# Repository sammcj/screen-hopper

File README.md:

# Screen Hopper: a smart KVM switch

This is a USB input switcher that lets you use you mouse and keyboard with two computers by just dragging the mouse cursor from one screen to the other. It's like Logitech Flow, Mouse without Borders, Synergy or Apple Universal Control, but it works entirely in hardware. No special software is required on the computers. It works with Windows, Linux and Mac.

Here's a [demo video](https://www.youtube.com/watch?v=z24jG9Nh5gk).

This project is derived from [HID Remapper](https://github.com/jfedor2/hid-remapper) so it inherits all the nice features like input remapping, sensitivity adjustment, polling rate overclocking and more. Check out that project's documentation to see its full potential.

Screen shapes and their relative position are configurable [through a web browser](https://www.jfedor.org/screen-hopper-config/) using WebHID (Chrome or Chrome-based browser required).

In addition to dragging the cursor from one screen to the other, you can also map a key or button to switch between screens.

Wireless receivers are supported and multiple devices can be connected at the same time using a USB hub.

## Profiles

Pico A stores up to 4 independent profiles. Each profile has its own screens, mappings, sensitivity, edge-resistance and jiggler interval - nothing is shared - so you can switch between, say, a single-monitor layout and a multi-monitor layout without re-running the configuration tool. Profiles are managed from the web tool (Profile tabs + active-profile selector) or directly in the multi-profile JSON shape (`{ "version": 8, "active_profile": 0, "profiles": [...] }`).

Bind any key or button to one of these target usages to switch profiles live:

- `0xfff30000` - cycle to the next profile
- `0xfff30001` .. `0xfff30004` - jump directly to profile 1..4

The hotkey lives inside each profile's own mappings, so include it in every profile you want to be able to leave.

## Keep-awake jiggler

Set a profile's `jiggle_interval` (seconds) to have Pico A nudge whichever machine has been idle longest, stopping the inactive side from locking while you work on the other. Idleness is tracked per output, so using one machine doesn't reset the other's clock.

Bind any source to target usage `0xfff30010` for a runtime on/off toggle - the onboard LED blinks **3 times for ON, 5 times for OFF**. The toggle does not change the persisted interval; it only enables/disables the jiggler for the current power cycle. When the toggle turns the jiggler ON, the cursor on the forwarder machine does a brief down/up/right/left sweep (~250 px each way, returning to where it started) so you can see the toggle landed without looking at the LED.

## Pointer upsampling (experimental)

A 125 Hz mouse (MX Master and similar) hands Pico A one position every 8 ms while the local Mac polls at 1 kHz. With no button held, Pico A walks each new sample out linearly over the following 8 ms in 1 ms steps, so the host sees ~1 kHz updates instead of 8 ms hops. This trades one sample interval of pointer latency for a smoother cursor on 60 Hz displays. Local machine only; drags and everything relative are untouched. On by default. Bind a source to `0xfff30011` to toggle it at runtime (3 blinks on, 5 off). Not persisted.

## Type text from the clipboard

`config-tool/type_text.py` ships a small CLI that turns text on the Pico-A computer into keystrokes on the forwarder machine, useful for passing a URL, a code snippet or a short password across without needing networking or host software on the second computer.

```shell
pbpaste | python3 config-tool/type_text.py    # macOS clipboard
python3 config-tool/type_text.py < file.txt   # from a file
python3 config-tool/type_text.py              # falls back to pbpaste on macOS
```

To fire it from anywhere with a hotkey, bind a shortcut in a tool like BetterTouchTool to
an "Execute Shell Script" action running `pbpaste | python3 config-tool/type_text.py`. Use
absolute paths (the script's Python and `pbpaste`), because such tools run scripts in a
minimal shell without your normal `PATH`, and pipe `pbpaste` in explicitly rather than
relying on the clipboard fallback.

The text is buffered on Pico A (cap: 4096 bytes - longer input is truncated) and replayed at ~70 characters/second through the forwarder's USB HID keyboard interface. Bytes outside printable US-ASCII (plus tab and newline) are dropped by the firmware, so the CLI transliterates non-ASCII first: box drawing becomes `+-|`, smart quotes and dashes become their ASCII forms, accents are stripped (`café` -> `cafe`), symbols get spelled out (`©` -> `(c)`, `½` -> `1/2`, `⌘` -> `cmd`), and ANSI colour escapes plus stray control bytes are removed. Characters with no ASCII form at all (emoji, CJK, Greek) are dropped and listed as a warning. Pass `--raw` to send the bytes untouched; anything still unsupported is listed and the CLI exits unless you pass `--force`. The remote machine must be on a US keyboard layout for punctuation to land correctly; letters and digits are layout-independent.

## How is it possible?

As you might know, normal mice only send relative inputs (X/Y deltas) to the computer, they don't know where the cursor is on the screen. Screen Hopper needs to know this to be able to switch between the screens. So what it does is it keeps an internal state of where the cursor is based on the inputs received from the mouse and it sends the absolute X/Y position to the connected computers. It is a standard feature of the USB HID protocol, but normally it's only used by devices like touchscreens and graphic tablets.

There are some consequences to this mode of operation, for example the aspect ratios of the screens used need to be configured for Screen Hopper to be able to properly scale the horizontal and vertical inputs. Also it probably won't work very well with games that expect raw mouse inputs.

## How to make the device

There are two hardware versions of the Screen Hopper: the dual Pico version and the triple Pico version. They have the same functionality, but the triple Pico version has better device compatibility - some input devices work with either, but some will only work with the triple Pico version.

See [HARDWARE.md](HARDWARE.md) for details on how to make both versions of the device.

## How to use the configuration tool

A live version of the web configuration tool can be found [here](https://www.jfedor.org/screen-hopper-config/). It only works in Chrome and Chrome-based browsers. On Linux you might need to give yourself permissions to the appropriate `/dev/hidraw*` device. The configuration tool should be used on the computer connected to the Pico running `screenhopper.uf2` or `screenhopper_a.uf2`.

Some of the configuration options are inherited from [HID Remapper](https://github.com/jfedor2/hid-remapper) so check that project for the meaning of those settings (the mapping functionality can do really awesome things!).

Screen Hopper needs to know the screen shapes and their relative position to be able to move the cursor between the two computers. You configure that by entering the position (X, Y) and dimensions (width, height) of each screen. (A graphical preview would be nice here, but for now it's just numbers.) The dimensions use abstract units so their absolute values don't mean much, but you will find some combinations give you reasonable mouse sensitivity. You can adjust the sensitivity for each screen separately.

The "Restrict cursor" setting determines what should happen when you drag the mouse cursor outside of the screens (to the area that's not visible). If you select the "to screens" option, it will not be possible to go outside the visible area. If you select the "to bounding box" option, the cursor will be restricted to the smallest rectangle that covers both screens (this only makes a difference if the touching edges of the two screens are not the same length). If you select "don't restrict", the cursor will not stop at any of the screen edges.

Depending on the screens configuration and the "Restrict cursor" setting, it might be possible for the cursor to be outside of the visible area. There's a separate setting for mouse sensitivity for that situation.

If you configure the screens so that they don't touch each other (there's a gap) and select the "restrict to screens" option then it will not be possible to drag the cursor from one screen to the other. You can still switch between the screens by mapping some key or button to "Switch screen".

If you can't use the browser-based configuration tool, there's also a [command-line tool](config-tool) that takes JSON in the same format as the web tool on standard input. I only tested it on Linux, but in theory it should also run on Windows and Mac.

## How to compile the firmware

Both Raspberry Pi Pico (RP2040) and Pico 2 (RP2350) are supported.

```shell
git clone https://github.com/jfedor2/screen-hopper.git
cd screen-hopper/firmware

# for pico v1:
make pico1

# for pico v2:
make pico2
```

### Firmware output

After building, the UF2 firmware files are copied to `firmware/pico1/` or `firmware/pico2/`:

| File                 | Version | Purpose                  |
| -------------------- | ------- | ------------------------ |
| `screenhopper.uf2`   | Dual    | Main Pico (with PIO-USB) |
| `forwarder.uf2`      | Dual    | Second Pico              |
| `screenhopper_a.uf2` | Triple  | Pico A                   |
| `screenhopper_b.uf2` | Triple  | Pico B (USB host)        |

To flash, hold BOOTSEL while plugging in the Pico, then copy the appropriate UF2 file to the drive that appears. Alternatively, `make flash TARGET=<a|b|forwarder|single> [BOARD=pico1|pico2] [CONFIG=path]` wraps the whole thing - it builds (re-baking if `CONFIG=` is given), auto-detects the BOOTSEL volume and uses `picotool load -x` to flash and reboot, or falls back to a Raspberry Pi Debug Probe over SWD when no BOOTSEL device is present.

### Applying config changes without reflashing

For config-only edits (screens, mappings, profiles, jiggler interval, edge resistance) reach for `make apply-config CONFIG=path/to/config.json` instead of `make flash`. It pushes the JSON to the running Pico A over USB HID (live + persisted, no reboot) and also re-bakes `firmware/src/baked_config.h` so the next `make flash` carries the same default. Only Pico A holds screen/mapping config, so config changes never need Pico B or the forwarder reflashed. Verify what the firmware is actually running with `make get-config`.

### Baking a config into the firmware

Flashing a Pico does NOT erase the persisted config sector (it lives outside the UF2 image), but if a board has no persisted config yet, the firmware uses its baked default. Bake one in as a compile-time default by passing `CONFIG` to the build:

```shell
make pico2 CONFIG=../config-tool/config.json
```

The build runs `config-tool/bake_config.py`, which turns the JSON into the same flash-sector image the device would persist, and embeds it in `firmware/src/baked_config.h`. On boot, a config persisted over USB still wins; the baked config is the fallback used when flash holds none (so a freshly flashed board comes up configured without running the configuration tool). The JSON can be a legacy single-profile shape or the multi-profile shape (`{ "version": 8, "active_profile": 0, "profiles": [...] }`).

`CONFIG` is sticky: once baked, plain `make pico2` keeps it across rebuilds. To clear it, build with an empty value, `make bake CONFIG=`. The generated `firmware/src/baked_config.h` is gitignored, so a baked personal config is never committed. A build with no baked config uses the firmware's built-in defaults as before.

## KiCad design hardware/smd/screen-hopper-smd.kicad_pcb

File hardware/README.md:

# Screen Hopper - triple Pico 2 carrier PCB

A carrier board for the triple-Pico version of Screen Hopper. The three Raspberry Pi Pico 2 boards, a high-speed optocoupler, the two resistors, a bypass capacitor and a USB-A host port all mount on one PCB, replacing the breadboard and jumper wires described in [HARDWARE.md](../HARDWARE.md).

Four variants are provided from the same netlist:

| Variant | Folder | Size | Assembly |
| ------- | ------ | ---- | -------- |
| Compact SMD | [`smd/`](smd/) | 92 x 82 mm | Optocoupler + passives reflowed by the fab; you mount the three Picos flat, single-sided |
| Through-hole | [`tht/`](tht/) | 112 x 106 mm | You solder everything; Picos A and Forwarder on headers |
| Double-sided | [`compact/`](compact/) | 81 x 59 mm | Smallest by area. Pico B reflows on the back under Pico A; adds a USB-C host port |
| Plug-in header | [`header/`](header/) | 54 x 60 mm | No Pico reflow - all three Picos plug into 0.1" pin-headers. No host connector (device uses Pico B's micro-USB). Fab places only the opto + 3 passives |

The double-sided `compact` variant is the smallest board. It stacks Pico B on the back copper directly beneath Pico A and offers both a USB-C and a USB-A host receptacle - **populate only one** (see [Host connector](#host-connector-compact-variant)). It needs the finer JLCPCB 6/6 process (0.2 mm tracks, 0.15 mm clearance, 0.5/0.3 mm vias) to fan out the 0.5 mm-pitch USB-C, where the other two run on the relaxed cheap-everywhere rules.

The `header` variant exists so you never reflow a Pico. All three Picos plug into 0.1" pin-headers (soldering a straight header strip is far easier than reflowing a castellated module), so the fab only places the SMD optocoupler and its three passives. Pico A is on the front top row and Pico B on the back directly behind it; because two through-hole Picos can't share holes, Pico B's hole grid is **offset by 8.89 mm** (half the 17.78 mm row spacing) so the grids interleave. There is no on-board host connector: the mouse/keyboard plugs into Pico B's own micro-USB through an OTG adapter (the same D-/D+/VBUS/GND lines the other variants route to a receptacle), which is what keeps this board small and simple. It uses the same fine 6/6 process as `compact` for the dense interleaved Pico holes. See [Plug-in header variant](#plug-in-header-variant).

## The one thing that matters: galvanic isolation

The optocoupler exists to keep the two host computers electrically isolated. Pico A and Pico B share power and ground fed from computer 1 (and the input device); the Forwarder runs on its own power and ground fed from computer 2. The only connection between the two sides is the optocoupler's internal LED-to-phototransistor light path.

The board enforces this with **two separate ground/power nets** (`GND1`/`VBUS1` and `GND2`/`VBUS2`) and a **copper keepout gap under the optocoupler** that no track or pour may cross. Domain 1 copper stops just left of the opto's input pins; domain 2 copper starts just right of its output pins. Do not bridge the two sides with a wire, a ground pour, or a mounting screw/standoff that ties the grounds together - that defeats the isolation and can create a ground loop between two separate computers.

## What to send to the PCB fab

For a **bare board** (any variant), upload the gerber zip:

- `smd/screen-hopper-smd-gerbers.zip`, `tht/screen-hopper-tht-gerbers.zip`, `compact/screen-hopper-compact-gerbers.zip` or `header/screen-hopper-header-gerbers.zip`

Fab settings: **2 layers, 1.6 mm FR-4, 1 oz copper, HASL or ENIG**. The `smd`/`tht` boards use 0.35 mm tracks, 0.2 mm clearance and 0.35 mm drills, which every fab (PCBWay, JLCPCB, etc.) handles at the cheapest tier. The `compact` board needs 0.2 mm tracks, 0.15 mm clearance and 0.3 mm drills to escape the USB-C, and the `header` board uses the same finer rules to route between its dense interleaved Pico holes - order both from **JLCPCB** (its standard 6/6 process and cheapest tier cover this).

For an **SMD board assembled** by the fab, also supply:

- `BOM-smd.csv`, `BOM-compact.csv` or `BOM-header.csv` - bill of materials
- the matching `-positions.csv` - centroid / pick-and-place file

The fab can place the optocoupler (SOIC-8), the 0805 resistors and the 0805 capacitor (and, on `compact`/`header`, the SMD USB-C receptacle, the two CC resistors and the SOT-23-6 ESD array). The three Pico 2 modules are not standard catalogue parts, so either hand-solder them onto the castellated pads yourself or consign them to the fab. On `smd`/`tht` the USB-A receptacle is a through-hole vertical part, hand-soldered. On `compact` the USB-A is a horizontal edge-mount part with SMD contacts the fab can place plus two through-hole shield posts you solder by hand for mechanical strength. The `compact` board places parts on **both sides** - tell the fab it is a double-sided assembly (Pico B is the only part on the back). On `header` the fab places only the four front-side SMD parts (opto, two resistors, bypass cap); the three Picos are 0.1" through-hole parts you fit yourself, flagged DNP in the Rev0 BOM. There is no host connector - the device plugs into Pico B's micro-USB.

## Bill of materials

See [`BOM-smd.csv`](BOM-smd.csv), [`BOM-tht.csv`](BOM-tht.csv), [`BOM-compact.csv`](BOM-compact.csv) and [`BOM-header.csv`](BOM-header.csv). Summary:

| Ref | Part | SMD | THT | Compact | Header |
| --- | ---- | --- | --- | ------- | ------ |
| A1, A2, A3 | Raspberry Pi Pico 2 (x3) | flat castellated mount | A/Fwd on headers, B flat | flat; B on the back under A | all on 0.1" headers; B on the back, grid offset 8.89 mm |
| U1 | High-speed optocoupler | HCPL-0601 (SO-8) | 6N137 (DIP-8 + socket) | HCPL-0601 (SO-8) | HCPL-0601 (SO-8) |
| R1 | 470 R (opto LED limit) | 0805 | axial 1/4 W | 0805 | 0805 |
| R2 | 680 R (opto VO pull-up) | 0805 | axial 1/4 W | 0805 | 0805 |
| R3, R4 | 56 k (USB-C CC pull-ups) | - | - | 0805 | - |
| C1 | 100 nF (opto bypass) | 0805 | ceramic disc | 0805 | 0805 |
| J1 | USB-A receptacle (host) | through-hole (vertical) | through-hole (vertical) | horizontal edge-mount (SMD + posts) | - |
| J2 | USB-C receptacle (host) | - | - | SMD 16-pin | - |
| U2 | USBLC6-2SC6 USB ESD array | - | - | SOT-23-6 | - |

Suggested MPNs in the CSVs are starting points - confirm against your supplier's stock.

U1 note: the **6N137 has no true SO-8 package** - its surface-mount form is a wide gull-wing DIP (~10 mm span, 2.54 mm pitch) that does not fit an SO-8 land. The SO-8 builds (smd, compact, header) use the **HCPL-0601** (Broadcom; same family, identical pinout, true SO-8; HCPL-0611 is a higher-CMR drop-in). Only the through-hole build uses a real 6N137, in a DIP-8 socket.

### Host connector (compact variant)

The `compact` board carries **both** a USB-A (`J1`) and a USB-C (`J2`) host receptacle, both horizontal edge-mount parts whose openings face the left board edge, wired to the same D+/D- lines on Pico B's native USB. **Populate and use only one** - they share the data lines, so fitting both and plugging a device into each shorts two devices together. The USB-C port is wired as a host (downstream-facing): `R3`/`R4` (56 k) pull CC1/CC2 up to VBUS to advertise default USB power to whatever plugs in. Leave `R3`/`R4` and `J2` unpopulated if you only want USB-A, or leave `J1` off if you only want USB-C.

Both connectors are commonly-stocked cheap parts: the USB-C is the HRO TYPE-C-31-M-12 (LCSC C165948, a JLCPCB basic part), and the USB-A is a standard horizontal Type-A edge-mount (TE 292303-7 footprint; any equivalent fits the same pads). KiCad 10 ships no 3D model for the exact HRO USB-C footprint, so `J2`'s model is remapped in `build_board.py` to a near-identical 16-pin USB-C (`USB_C_Receptacle_GCT_USB4105...`) purely so the 3D viewer shows a body - the pads, gerbers and pick-and-place still come from the real HRO footprint.

### Plug-in header variant

The `header` board replaces every Pico's flat castellated footprint with a pair of 1x20 0.1" through-hole headers, so you solder a straight pin-header strip (easy) instead of reflowing a 40-pad castellated module (hard). Two things make the layout work:

- **Two-row stack, back-side Pico B.** Pico A sits on the front top row, the Forwarder on the front bottom row, and Pico B on the **back** directly behind Pico A. Two through-hole Picos cannot share holes, so Pico B's hole grid is shifted **8.89 mm** (half the 17.78 mm inter-row spacing) along the board so the two grids interleave - the nearest drilled holes of A and B clear each other by ~7.9 mm. The board is 54 x 60 mm.
- **No host connector.** The mouse/keyboard plugs into **Pico B's own micro-USB** (through a micro-USB OTG / host adapter). Pico B is the USB host; its native USB (D-/D+/VBUS/GND) is on that connector, electrically the same lines the `smd`/`tht`/`compact` boards route out to a USB-A/USB-C receptacle. Dropping the on-board receptacle (and the CC pull-ups, ESD array and USB tap header it needed) is what makes this the simplest, smallest variant. Trade-off: Pico B's micro-USB is also its BOOTSEL/flashing port, so unplug the input device when you reflash Pico B.

**Mounting the Picos - Pico B must sit in a socket.** Pico B (`A2`, on the back, stacked behind Pico A) is the one part that *requires* a female 0.1" socket strip (`SKT1` in the BOM, 2 x 1x20). Solder the socket into A2's hole rows from the back and clip its tails flush on the front; Pico B's own pins then plug into the socket body and never pass through the board. This is necessary because Pico A's pins, soldered on the front, protrude ~4.4 mm out the back (6 mm pins through a 1.6 mm board) directly under Pico B's body - the socket lifts Pico B ~8.5 mm clear so A's through-pins stop ~4 mm short of it (and the two pin grids interleave 8.89 mm apart, so the pins themselves never line up either). Pico A and the Forwarder sit on the front with nothing stacked over them, so they may be soldered to plain male pin-headers or socketed for easy swapping - your choice. The PCB is identical either way: a socket reuses the same plated holes, so it has no separate footprint (which is why it does not appear in the 3D render).

Silkscreen on the board names each Pico (Pico A / Pico B (back) / Forwarder), prints the corner pin numbers (1/20/21/40) for each Pico, and carries a one-line signal legend (A<->B serial on GP0-3, opto on A.GP20 / Fwd.GP9, host = Pico B micro-USB).

The fab populates only the four SMD parts (`U1`, `R1`, `R2`, `C1`); the three Picos are flagged DNP in [`header/Rev0_BOM-screen-hopper-header.csv`](header/Rev0_BOM-screen-hopper-header.csv) since you fit them by hand. Every populated MPN in the Rev0 BOM was confirmed to return itself as an exact in-stock match in NextPCB's catalogue, so the no-review automated matcher sources them without substituting a wrong value. Ground is poured per-domain (`GND1` on the host side, `GND2` on the Forwarder side) and floods stop short of the isolation gap; a few inner GND pins the autorouter leaves stranded are tied in with explicit stitch tracks, so the board verifies at 0 unconnected.

## Schematic

Each variant ships an editable KiCad schematic alongside its board:

- `smd/screen-hopper-smd.kicad_sch`
- `tht/screen-hopper-tht.kicad_sch`
- `compact/screen-hopper-compact.kicad_sch`

Upload this `.kicad_sch` to tools that ask for one (e.g. Quilter, which uses it to group related components and assign bypass capacitors). It carries the same netlist as the board, so the connectivity matches. A rendered overview is in [`schematic.svg`](schematic.svg).

## Wiring

Authoritative net list:

| Net | Connections |
| --- | ----------- |
| UART0 (A<->B) | A.GPIO0-B.GPIO1, A.GPIO1-B.GPIO0, A.GPIO2-B.GPIO3, A.GPIO3-B.GPIO2 |
| VBUS1 | A.VBUS, B.VBUS, J1.VBUS (header: no J1 - VBUS1 is just A.VBUS + B.VBUS) |
| GND1 | A.GND, B.GND, J1.GND + shield, B.TP1 (header: just A.GND + B.GND) |
| Opto TX | A.3V3 - R1(470) - U1.2 (anode); U1.3 (cathode) - A.GPIO20 |
| USB host | J1.D- - B.TP2 (USB_DM); J1.D+ - B.TP3 (USB_DP). Header has no on-board host port - the device uses Pico B's own micro-USB |
| ESD (compact only) | U2.I/O1 (pins 1,6) - USB_DP; U2.I/O2 (pins 3,4) - USB_DM; U2.VBUS (5) - VBUS1; U2.GND (2) - GND1 |
| VBUS2 | Fwd.VBUS - U1.8 (VCC) - C1 |
| GND2 | Fwd.GND - U1.5 (GND) - C1 |
| Opto RX | Fwd.3V3 - R2(680) - U1.6 (VO); Fwd.GPIO9 - U1.6 (VO) |

`C1` (100 nF) bypasses the optocoupler's VCC (pin 8) to GND (pin 5) - recommended by the 6N137 datasheet. Optocoupler pin 7 (VE, enable) is left unconnected, matching the working breadboard build (the 6N137's internal pull-down on VE leaves it enabled).

Two deliberate choices, both inherited from the proven breadboard build:

- **`R1` = 470 Ω** sets the opto LED drive to roughly 3.8 mA from the 3.3 V rail. That is slightly below the 6N137's typical 5 mA recommended forward current, but it switches reliably at 1 Mbaud on the breadboard and stays well clear of the LED's 20 mA limit. If you want more margin you can drop to ~330 Ω (about 5.7 mA); leave it at 470 Ω to match the validated design.
- **ESD protection** (`U2`, compact variant only): a USBLC6-2SC6 low-capacitance TVS array sits next to the host connectors and clamps the D+/D- lines to VBUS1/GND1, shunting a static-discharge spike to ground before it reaches Pico B's USB transceiver. It's invisible during normal operation and adds negligible capacitance at full-speed HID rates. It's in domain 1 only and has no effect on the galvanic isolation. The `smd`/`tht` boards omit it (matching the original build); add equivalent protection there yourself if you want it.

## Unplaced board (for external auto-placers)

`make unplaced` writes a board per variant with every footprint loaded and the full netlist assigned, but **no placement and no routing** - the parts are parked in a column just right of an empty board outline:

- `unplaced/screen-hopper-smd-unplaced.kicad_pcb` (95 x 85 mm outline)
- `unplaced/screen-hopper-tht-unplaced.kicad_pcb` (115 x 110 mm outline)
- matching `.kicad_sch` for tools that also want the schematic

Feed one of these to an auto-placement tool, then route it (or let the tool route). Two things the tool won't know about, so check them in the result:

- **Galvanic isolation.** The placer sees `GND1`/`VBUS1` and `GND2`/`VBUS2` as distinct nets but has no reason to keep the two domains physically apart. After placement, confirm domain 2 (the Forwarder `A3`, opto output pins 5/6/8, `C1`, `R2`) sits on one side and everything else on the other, with the optocoupler straddling the boundary and a clear copper gap between - see the isolation section above. The hand-placed boards in `smd/` and `tht/` already do this.
- **Pico B orientation.** Its USB test points (TP1/2/3) must face the USB-A receptacle `J1`.

## Assembly notes

- **Pico B is always SMD-mounted flat**, even on the through-hole board. The USB-A host port wires to Pico B's native USB through its bottom test points (TP1/TP2/TP3 = USB_GND/USB_DM/USB_DP), and only the flat (castellated) footprint exposes those pads.
- **Pico B's micro-USB connector shares the same D+/D- lines as the USB-A port.** Leave Pico B's micro-USB unplugged in normal use - plug it in only to flash Pico B (BOOTSEL).
- **Flashing**: Pico A gets `screenhopper_a.uf2`, Pico B gets `screenhopper_b.uf2`, the Forwarder gets `forwarder.uf2`. Reflash by holding BOOTSEL while connecting that Pico's micro-USB to a computer. Re-upload your config to Pico A afterwards.
- **No ground pour** on `smd`/`tht`/`compact` - ground is routed as copper tracks. For lower EMI you can open the `.kicad_pcb` in KiCad, add a `GND1` zone on the left domain and a `GND2` zone on the right domain (keep them clear of the isolation gap), and refill. The `header` board already pours both domains (the two-row layout strands inner GND pins that pours plus stitch tracks tidy up).
- **No mounting holes** are placed (to avoid accidentally bridging the two ground domains through a metal standoff). Add your own in KiCad if you need them - keep any in the isolation gap non-plated, and don't let a screw or standoff connect domain-1 ground to domain-2 ground.
- **Compact variant is double-sided.** Pico A reflows on the top, Pico B on the back directly beneath it (the only back-side part). Reflow or hand-solder the back first, then the top, or have the fab do both. The USB-C host port (`J2`) and USB-A (`J1`) are mutually exclusive - see [Host connector](#host-connector-compact-variant).

## Regenerating

The boards are generated, routed and verified by scripts in [`lib/`](lib/):

```sh
cd hardware
make all      # build + autoroute + verify + export gerbers for all four variants
make check    # re-run the geometry checks on the built boards
make clean    # delete generated boards and fab files
# or build one: make smd | make tht | make compact | make header
```

Requirements: KiCad 10 (provides the bundled `pcbnew` Python module and `kicad-cli`) and a Java runtime. Download `freerouting.jar` (v2.x, from the freerouting GitHub releases) into `lib/`.

Pipeline: `build_board.py` places the parts and defines the netlist with `pcbnew`, exports a Specctra DSN, the freerouting autorouter routes it, the routes are imported back, and `kicad-cli` exports the gerbers/drill/centroid. `gen_sch.py` then writes the matching `.kicad_sch` and `check_sch.py` verifies its netlist against the same net table.

## Verification

`kicad-cli pcb drc` crashes on this macOS/KiCad 10.0.3 build (a tool bug, reproducible on an empty board), so verification runs through [`lib/check_board.py`](lib/check_board.py), which uses KiCad's own geometry engine to confirm, on every variant:

- **0 unconnected** nets (every pad reaches its net)
- **0 copper-clearance violations** - no different-net copper closer than each variant's design-rule clearance less a 0.02 mm rounding margin (so 0.18 mm for `smd`/`tht` whose rule is 0.2 mm; 0.13 mm for `compact`/`header` whose rule is 0.15 mm)
- **0 copper in the isolation gap** (domains bridged only by the optocoupler)

As a final belt-and-braces step before ordering, open the `.kicad_pcb` in KiCad and run **Inspect > Design Rules Checker** once, and eyeball the board against the wiring table above.

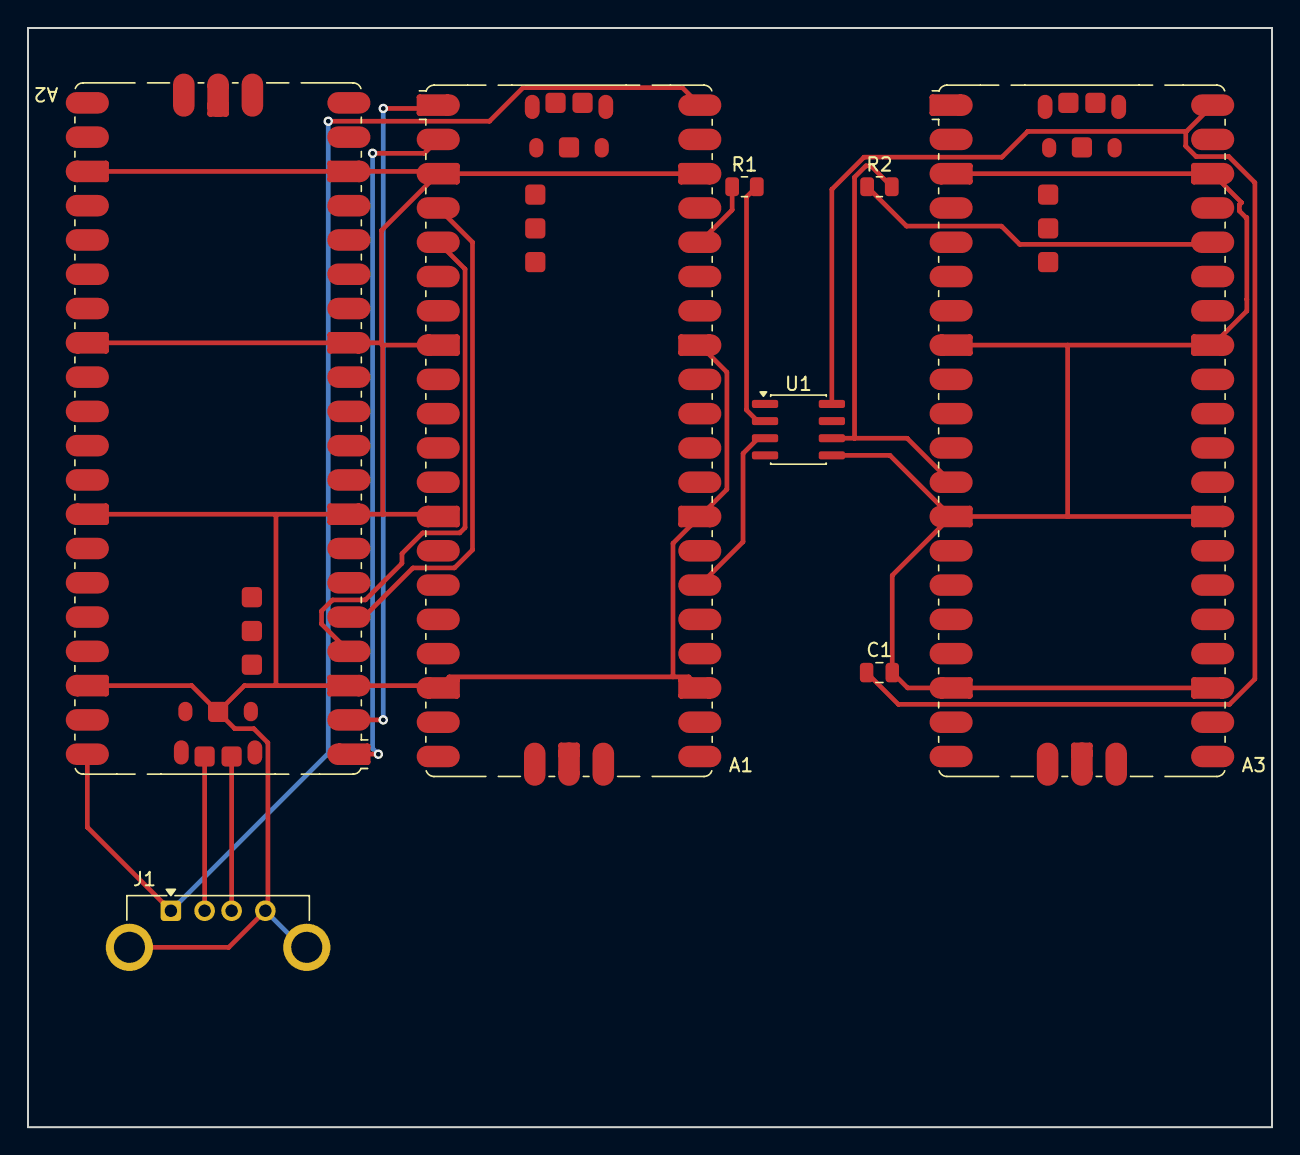
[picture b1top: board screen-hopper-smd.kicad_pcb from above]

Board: 2 copper layers, 92.2 x 81.4 mm, 8 parts (0 on the bottom side), 15 nets.

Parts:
A1: RP2350_PicoA; RaspberryPi_Pico_SMD
A2: RP2350_PicoB; RaspberryPi_Pico_SMD
A3: RP2350_Fwd; RaspberryPi_Pico_SMD
C1: 100nF; C_0805_2012Metric
J1: USB_A_Host; USB_A_Connfly_DS1095
R1: 470R; R_0805_2012Metric
R2: 680R; R_0805_2012Metric
U1: HCPL-0601; SOIC-8_3.9x4.9mm_P1.27mm

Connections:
FWD_3V3: A3.36, R2.1
GND1: A1.3, A1.8, A1.13, A1.18, A1.23, A1.28, A1.33, A1.38, A2.3, A2.8, A2.13, A2.18, A2.23, A2.28, A2.33, A2.38, A2.TP1, J1.4, J1.SH
GND2: A3.3, A3.8, A3.13, A3.18, A3.23, A3.28, A3.33, A3.38, C1.2, U1.5
OPTO_3V3: A1.36, R1.1
OPTO_ANODE: R1.2, U1.2
OPTO_CATH: A1.26, U1.3
OPTO_VO: A3.12, R2.2, U1.6
SER_A0_B1: A1.1, A2.2
SER_A1_B0: A1.2, A2.1
SER_A2_B3: A1.4, A2.5
SER_A3_B2: A1.5, A2.4
USB_DM: A2.TP2, J1.2
USB_DP: A2.TP3, J1.3
VBUS1: A1.40, A2.40, J1.1
VBUS2: A3.40, C1.1, U1.8

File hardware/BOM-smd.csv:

Reference,Qty,Value,Package,Description,Suggested MPN,Assembly,Notes
A1,1,RP2350_PicoA,RaspberryPi_Pico_SMD,Raspberry Pi Pico 2 (USB device to computer 1),Raspberry Pi SC1631,hand-solder / consign,Castellated edge-mount flat to board
A2,1,RP2350_PicoB,RaspberryPi_Pico_SMD,Raspberry Pi Pico 2 (USB host for mouse/keyboard),Raspberry Pi SC1631,hand-solder / consign,Must be non-W with castellations; USB test points TP1-3 used
A3,1,RP2350_Fwd,RaspberryPi_Pico_SMD,Raspberry Pi Pico 2 (forwarder to computer 2),Raspberry Pi SC1631,hand-solder / consign,Isolated domain 2
U1,1,HCPL-0601,SOIC-8,High-speed 10 Mbit SO-8 optocoupler (galvanic isolation),HCPL-0601 / HCPL-0611 (Broadcom; true SO-8),PCBWay SMT,SO-8 optocoupler. The 6N137 has no SO-8 package (DIP-8 / gull-wing only) - do NOT substitute it.
R1,1,470,R_0805_2012Metric,Resistor 470 ohm 1/8W 1% (opto LED current limit),generic 0805 470R,PCBWay SMT,Domain 1
R2,1,680,R_0805_2012Metric,Resistor 680 ohm 1/8W 1% (opto VO pull-up),generic 0805 680R,PCBWay SMT,Domain 2
C1,1,100nF,C_0805_2012Metric,Capacitor 100nF X7R 16V+ (opto VCC bypass),generic 0805 100nF X7R,PCBWay SMT,Domain 2; across opto pins 8-5
J1,1,USB_A_Host,USB_A_Connfly_DS1095,USB Type-A receptacle (mouse/keyboard input),Connfly DS1095-WNPxxx,hand-solder,Through-hole; wired to Pico B native USB

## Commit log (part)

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2026-03-04 feat(firmware): add USB remote wakeup support
    Set TUSB_DESC_CONFIG_ATT_REMOTE_WAKEUP in the USB configuration
    descriptor and send tud_remote_wakeup() once per suspend cycle when
    input is queued, allowing connected PCs to be woken from sleep by
    mouse/keyboard activity.
2026-03-25 feat: add support for pico2 and multi-monitor layouts
2026-05-22 feat: hardware board designs
2026-05-22 [automated commit or incremental update]
